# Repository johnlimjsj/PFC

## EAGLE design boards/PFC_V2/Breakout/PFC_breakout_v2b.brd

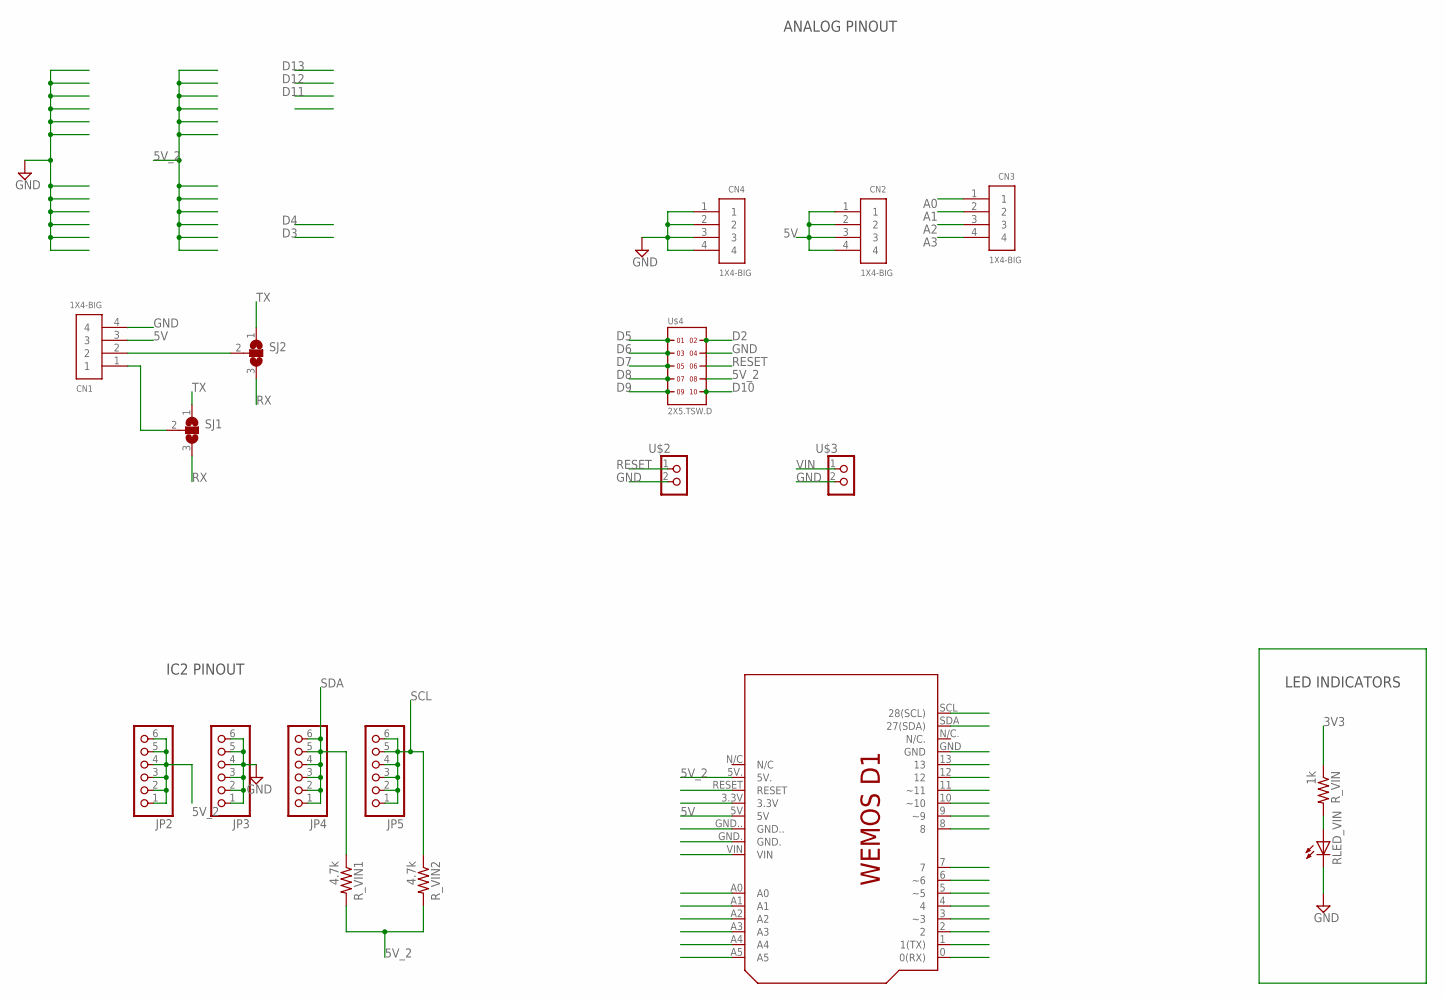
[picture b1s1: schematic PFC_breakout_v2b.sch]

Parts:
CN1, CN2, CN3, CN4: 1X4-BIG; 1X04-BIG
JP2, JP3, JP4, JP5: PINHD-1X6; 1X06
RLED_VIN: LEDCHIP-LED0603; CHIP-LED0603
R_VIN: 1k; R0603
R_VIN1, R_VIN2: 4.7k; R0603
SJ1, SJ2: SJ2W; SJ_2
U$1: WEMOS-D1SHIELD; WEMOS-D1
U$2, U$3: PINHD-2X1; 2X01
U$4: 2X5.TSW.D; TSW-105-XXX-D-XXX

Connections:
3V3: R_VIN.1, U$1.3.3V
5V: CN1.3, CN2.1, CN2.2, CN2.3, CN2.4, U$1.5V
5V_2: JP2.1, JP2.2, JP2.3, JP2.4, JP2.5, JP2.6, R_VIN1.2, R_VIN2.2, U$1.5V., U$4.8
A0: CN3.1, U$1.A0
A1: CN3.2, U$1.A1
A2: CN3.3, U$1.A2
A3: CN3.4, U$1.A3
A4: U$1.A4
A5: U$1.A5
D2: U$1.2, U$4.2
D3: U$1.3 (~3)
D4: U$1.4
D5: U$1.5 (~5), U$4.1
D6: U$1.6 (~6), U$4.3
D7: U$1.7, U$4.5
D8: U$1.8, U$4.7
D9: U$1.9 (~9), U$4.9
D10: U$1.10 (~10), U$4.10
D11: U$1.11 (~11)
D12: U$1.12
D13: U$1.13
GND: CN1.4, CN4.1, CN4.2, CN4.3, CN4.4, JP3.1, JP3.2, JP3.3, JP3.4, JP3.5, JP3.6, RLED_VIN.C, U$1.GND, U$1.GND., U$1.GND.., U$2.2 (3), U$3.2 (3), U$4.4
unnamed: RLED_VIN.A, R_VIN.2
unnamed: CN1.2, SJ2.2
unnamed: CN1.1, SJ1.2
RESET: U$1.RESET, U$2.1, U$4.6
RX: SJ1.3, SJ2.3, U$1.0 (0(RX))
SCL: JP5.1, JP5.2, JP5.3, JP5.4, JP5.5, JP5.6, R_VIN2.1, U$1.SCL (28(SCL))
SDA: JP4.1, JP4.2, JP4.3, JP4.4, JP4.5, JP4.6, R_VIN1.1, U$1.SDA (27(SDA))
TX: SJ1.1, SJ2.1, U$1.1 (1(TX))
VIN: U$1.VIN, U$3.1

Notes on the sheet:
ANALOG PINOUT
IC2 PINOUT
LED INDICATORS

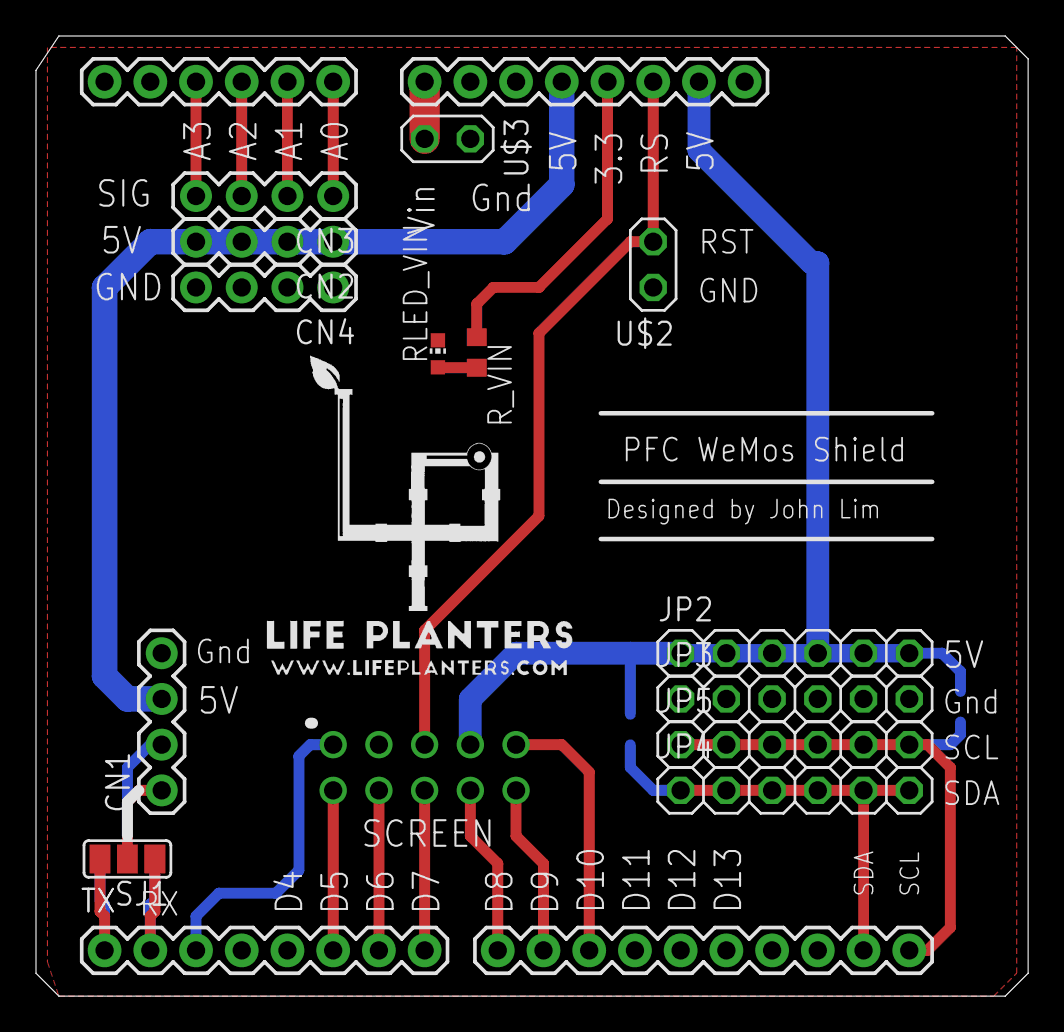
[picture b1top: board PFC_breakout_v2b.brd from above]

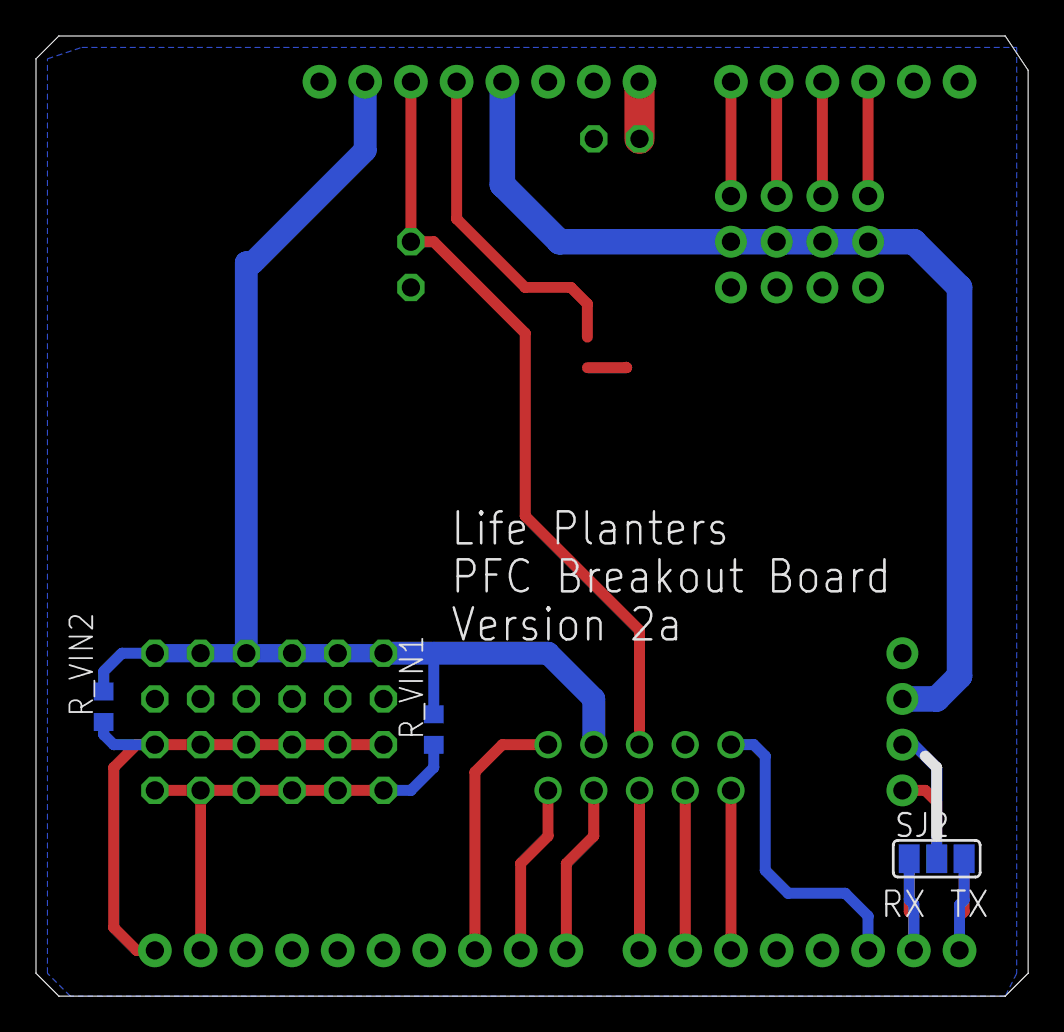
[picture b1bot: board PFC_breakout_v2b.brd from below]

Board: 2 copper layers, 55.1 x 53.3 mm, 18 parts (3 on the bottom side), 24 nets.

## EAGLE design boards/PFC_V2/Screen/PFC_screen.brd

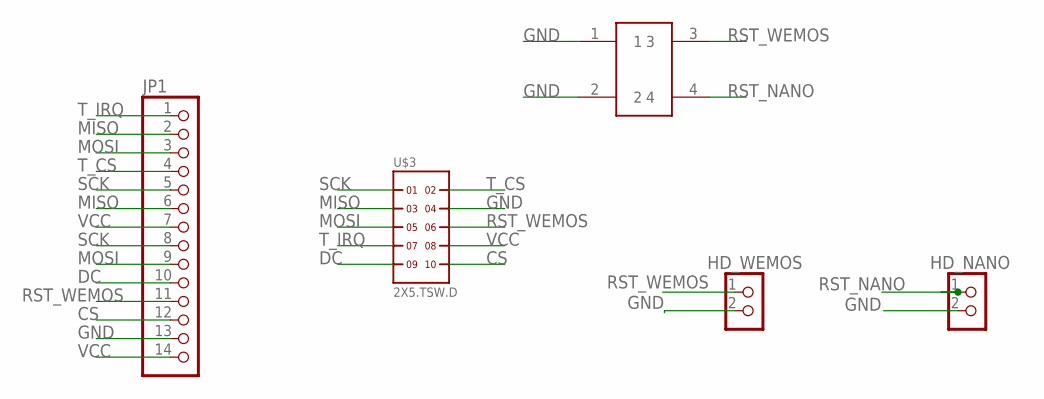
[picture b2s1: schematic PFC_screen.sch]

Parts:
HD_NANO: PINHD-2X1; 2X01
HD_WEMOS: PINHD-2X1; 2X01
JP1: PINHD-1X14-CB; 1X14-CB
U$1: EK1019; EK1019_6X6X5MM
U$3: 2X5.TSW.D; TSW-105-XXX-D-XXX

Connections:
CS: JP1.12, U$3.10
DC: JP1.10, U$3.9
GND: HD_NANO.2 (3), HD_WEMOS.2 (3), JP1.13, U$1.1, U$1.2, U$3.4
MISO: JP1.2, JP1.6, U$3.3
MOSI: JP1.3, JP1.9, U$3.5
RST_NANO: HD_NANO.1, U$1.4
RST_WEMOS: HD_WEMOS.1, JP1.11, U$1.3, U$3.6
SCK: JP1.5, JP1.8, U$3.1
T_CS: JP1.4, U$3.2
T_IRQ: JP1.1, U$3.7
VCC: JP1.7, JP1.14, U$3.8

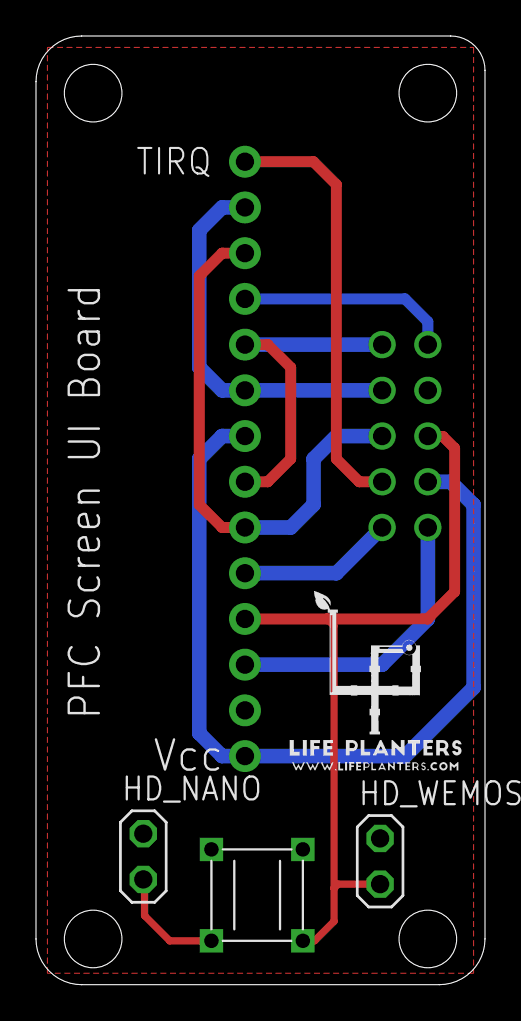
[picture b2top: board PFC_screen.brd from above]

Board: 2 copper layers, 24.9 x 52.7 mm, 5 parts (0 on the bottom side), 11 nets.

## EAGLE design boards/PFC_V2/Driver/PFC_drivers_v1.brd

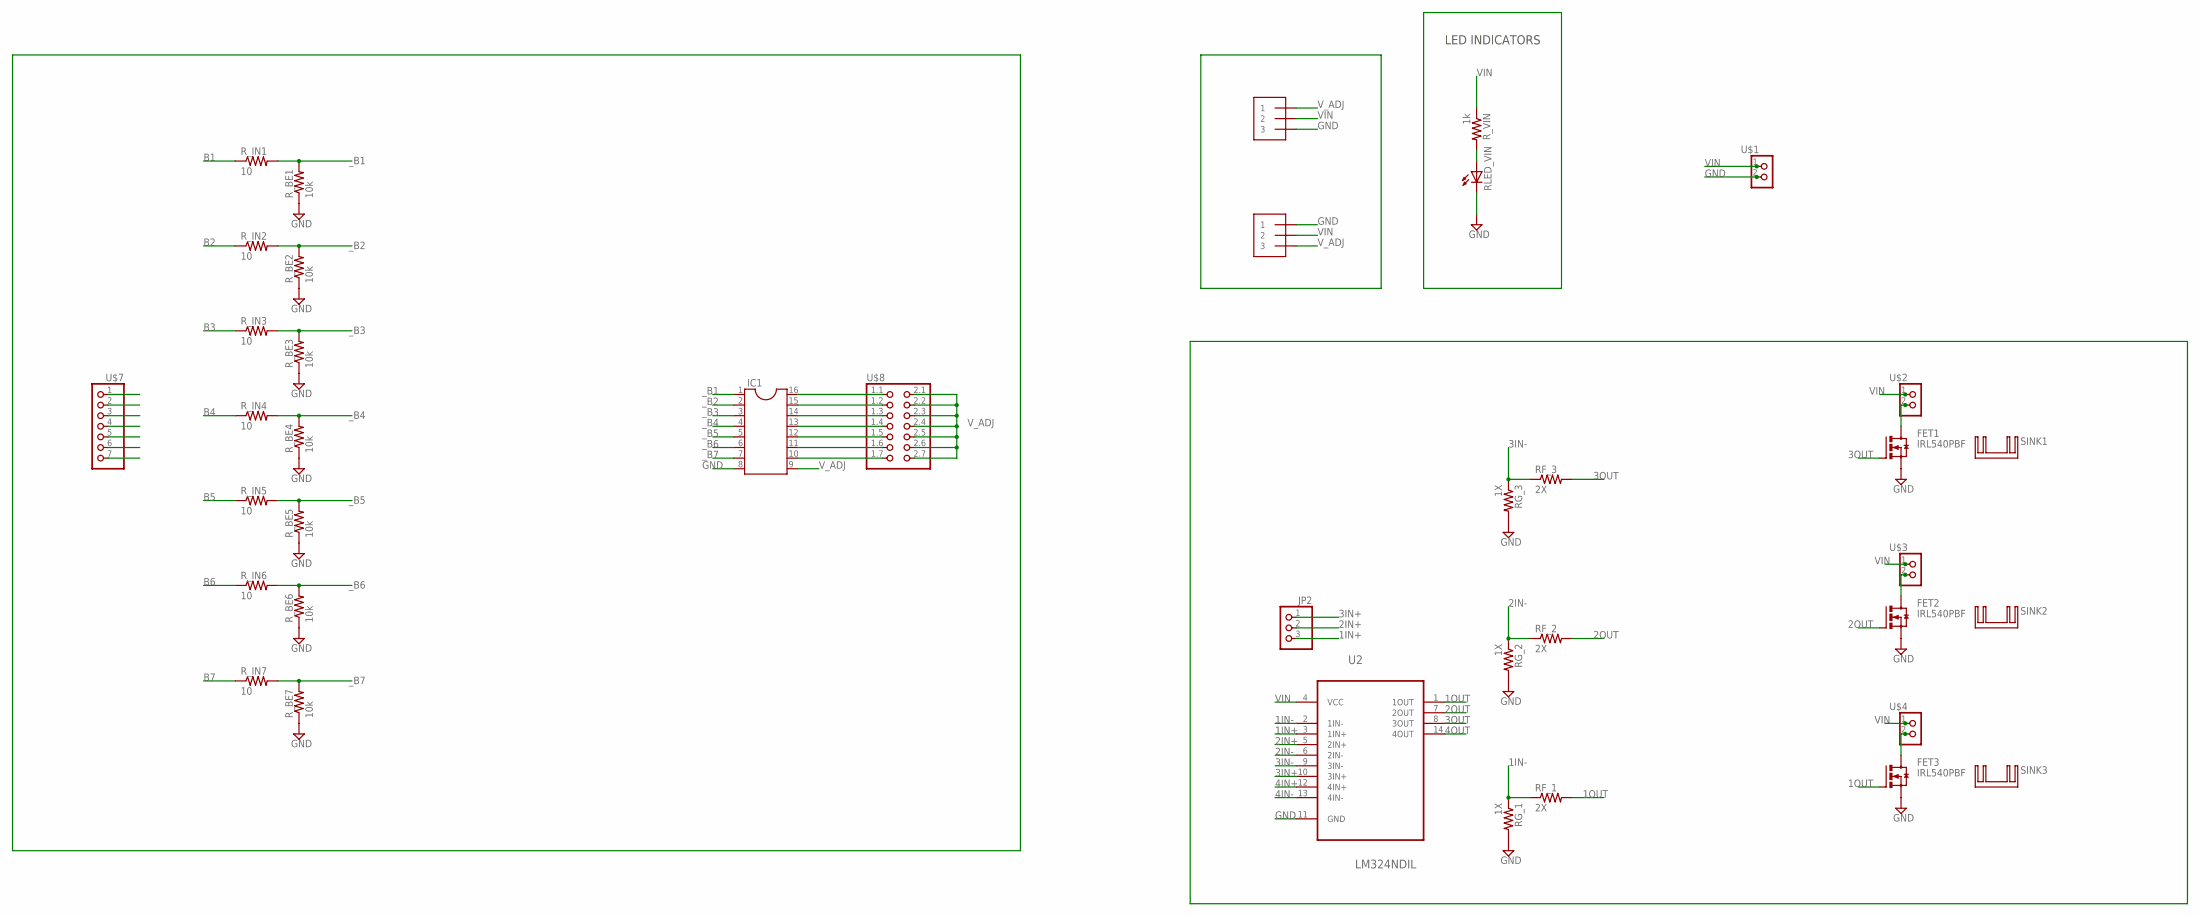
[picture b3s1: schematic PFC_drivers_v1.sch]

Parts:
FET1, FET2, FET3: IRL540PBF; TO220AV
IC1: DIL16S; SOCKET-16
JP2: PINHD-1X3; 1X03
RF_1, RF_2, RF_3: 2X; R0603
RG_1, RG_2, RG_3: 1X; R0603
RLED_VIN: LEDCHIP-LED0603; CHIP-LED0603
R_BE1, R_BE2, R_BE3, R_BE4, R_BE5, R_BE6, R_BE7: 10k; R0603
R_IN1, R_IN2, R_IN3, R_IN4, R_IN5, R_IN6, R_IN7: 10; R0603
R_VIN: 1k; R0603
SINK1, SINK2, SINK3: FW1S
U2: LM324NDIL; DIL14
U$1, U$2, U$3, U$4: PINHD-2X1; 2X01
U$5, U$6: 1X3; 1X3-3.5MM
U$7: PINHD-1X7; 1X07
U$8: PINHD-2X7; 2X07-BIG

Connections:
1IN+: JP2.3, U2.3 (1IN+)
1IN-: RF_1.1, RG_1.1, U2.2 (1IN-)
1OUT: FET3.B (G), RF_1.2, U2.1 (1OUT)
2IN+: JP2.2, U2.5 (2IN+)
2IN-: RF_2.1, RG_2.1, U2.6 (2IN-)
2OUT: FET2.B (G), RF_2.2, U2.7 (2OUT)
3IN+: JP2.1, U2.10 (3IN+)
3IN-: RF_3.1, RG_3.1, U2.9 (3IN-)
3OUT: FET1.B (G), RF_3.2, U2.8 (3OUT)
4IN+: U2.12 (4IN+)
4IN-: U2.13 (4IN-)
4OUT: U2.14 (4OUT)
B1: R_IN1.1, U$7.1
B2: R_IN2.1, U$7.2
B3: R_IN3.1, U$7.3
B4: R_IN4.1, U$7.4
B5: R_IN5.1, U$7.5
B6: R_IN6.1, U$7.6
B7: R_IN7.1, U$7.7
GND: FET1.E (S), FET2.E (S), FET3.E (S), IC1.8, RG_1.2, RG_2.2, RG_3.2, RLED_VIN.C, R_BE1.1, R_BE2.1, R_BE3.1, R_BE4.1, R_BE5.1, R_BE6.1, R_BE7.1, U2.11 (GND), U$1.2 (3), U$5.3, U$6.1
unnamed: RLED_VIN.A, R_VIN.2
unnamed: IC1.10, U$8.1.7
unnamed: IC1.11, U$8.1.6
unnamed: IC1.12, U$8.1.5
unnamed: IC1.13, U$8.1.4
unnamed: IC1.14, U$8.1.3
unnamed: IC1.15, U$8.1.2
unnamed: IC1.16, U$8.1.1
unnamed: FET1.C (D), U$2.2 (3)
unnamed: FET2.C (D), U$3.2 (3)
unnamed: FET3.C (D), U$4.2 (3)
VIN: R_VIN.1, U2.4 (VCC), U$1.1, U$2.1, U$3.1, U$4.1, U$5.2, U$6.2
V_ADJ: IC1.9, U$5.1, U$6.3, U$8.2.1, U$8.2.2, U$8.2.3, U$8.2.4, U$8.2.5, U$8.2.6, U$8.2.7
_B1: IC1.1, R_BE1.2, R_IN1.2
_B2: IC1.2, R_BE2.2, R_IN2.2
_B3: IC1.3, R_BE3.2, R_IN3.2
_B4: IC1.4, R_BE4.2, R_IN4.2
_B5: IC1.5, R_BE5.2, R_IN5.2
_B6: IC1.6, R_BE6.2, R_IN6.2
_B7: IC1.7, R_BE7.2, R_IN7.2

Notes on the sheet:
LED INDICATORS

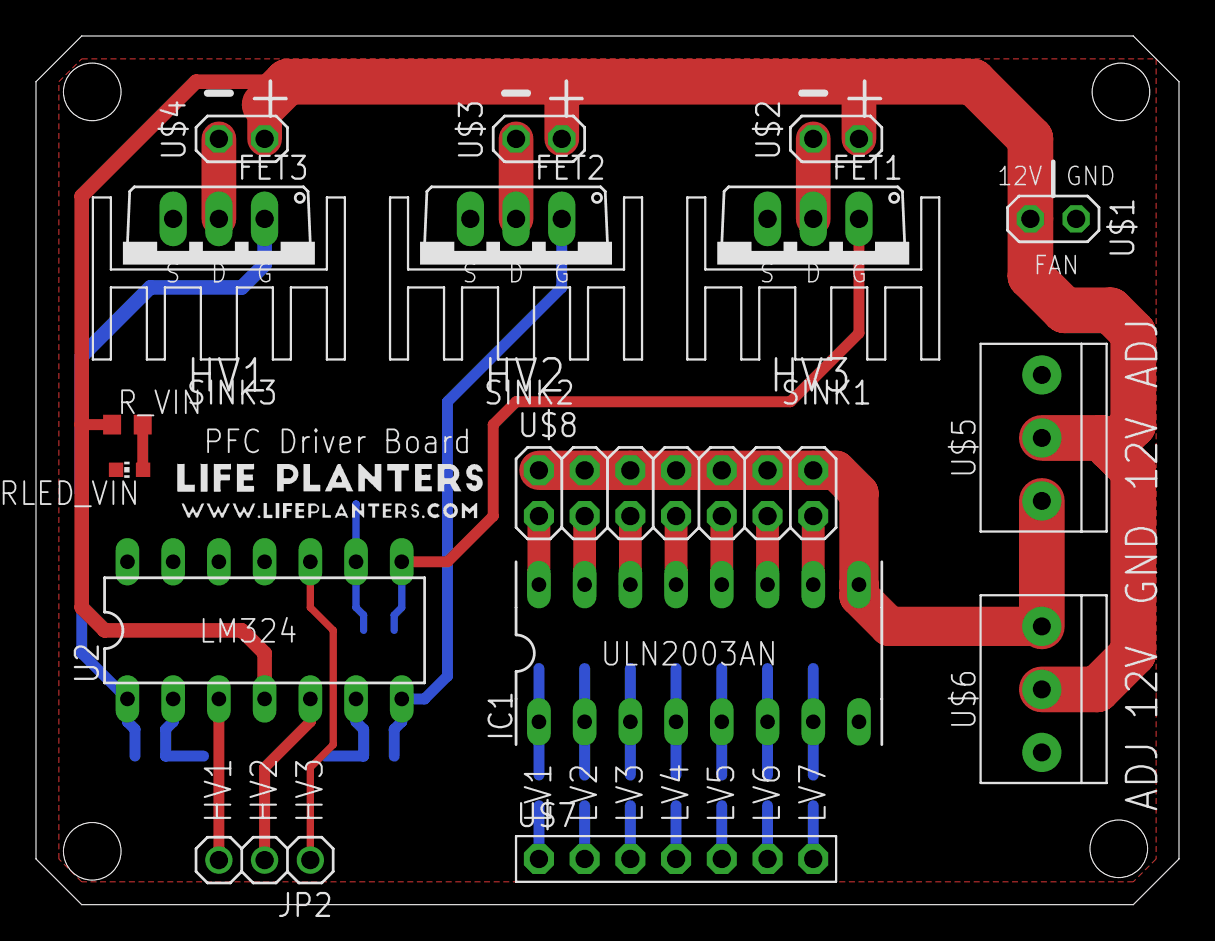
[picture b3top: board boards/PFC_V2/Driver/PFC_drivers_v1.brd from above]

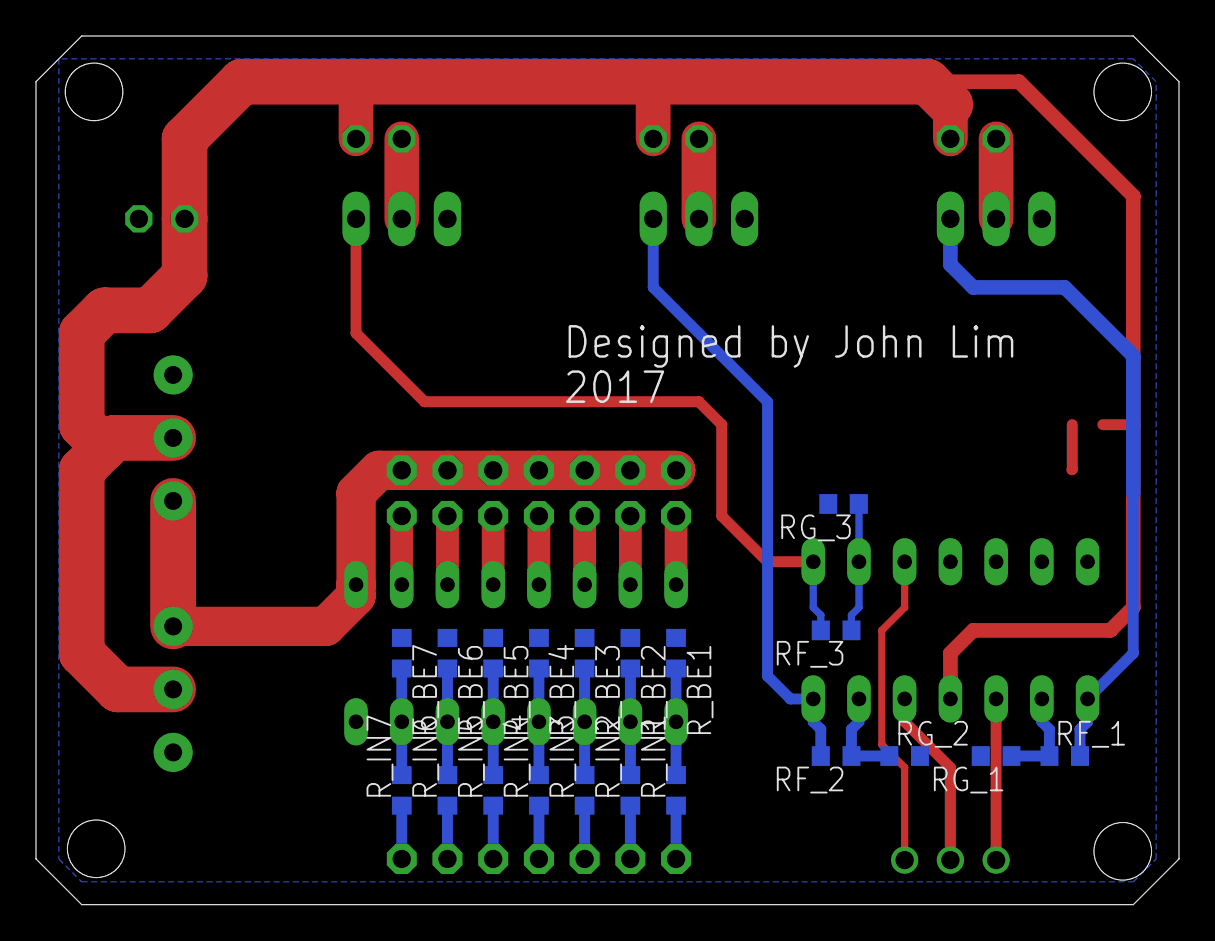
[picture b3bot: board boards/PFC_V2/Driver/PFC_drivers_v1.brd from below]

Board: 2 copper layers, 63.5 x 48.3 mm, 39 parts (20 on the bottom side), 37 nets.

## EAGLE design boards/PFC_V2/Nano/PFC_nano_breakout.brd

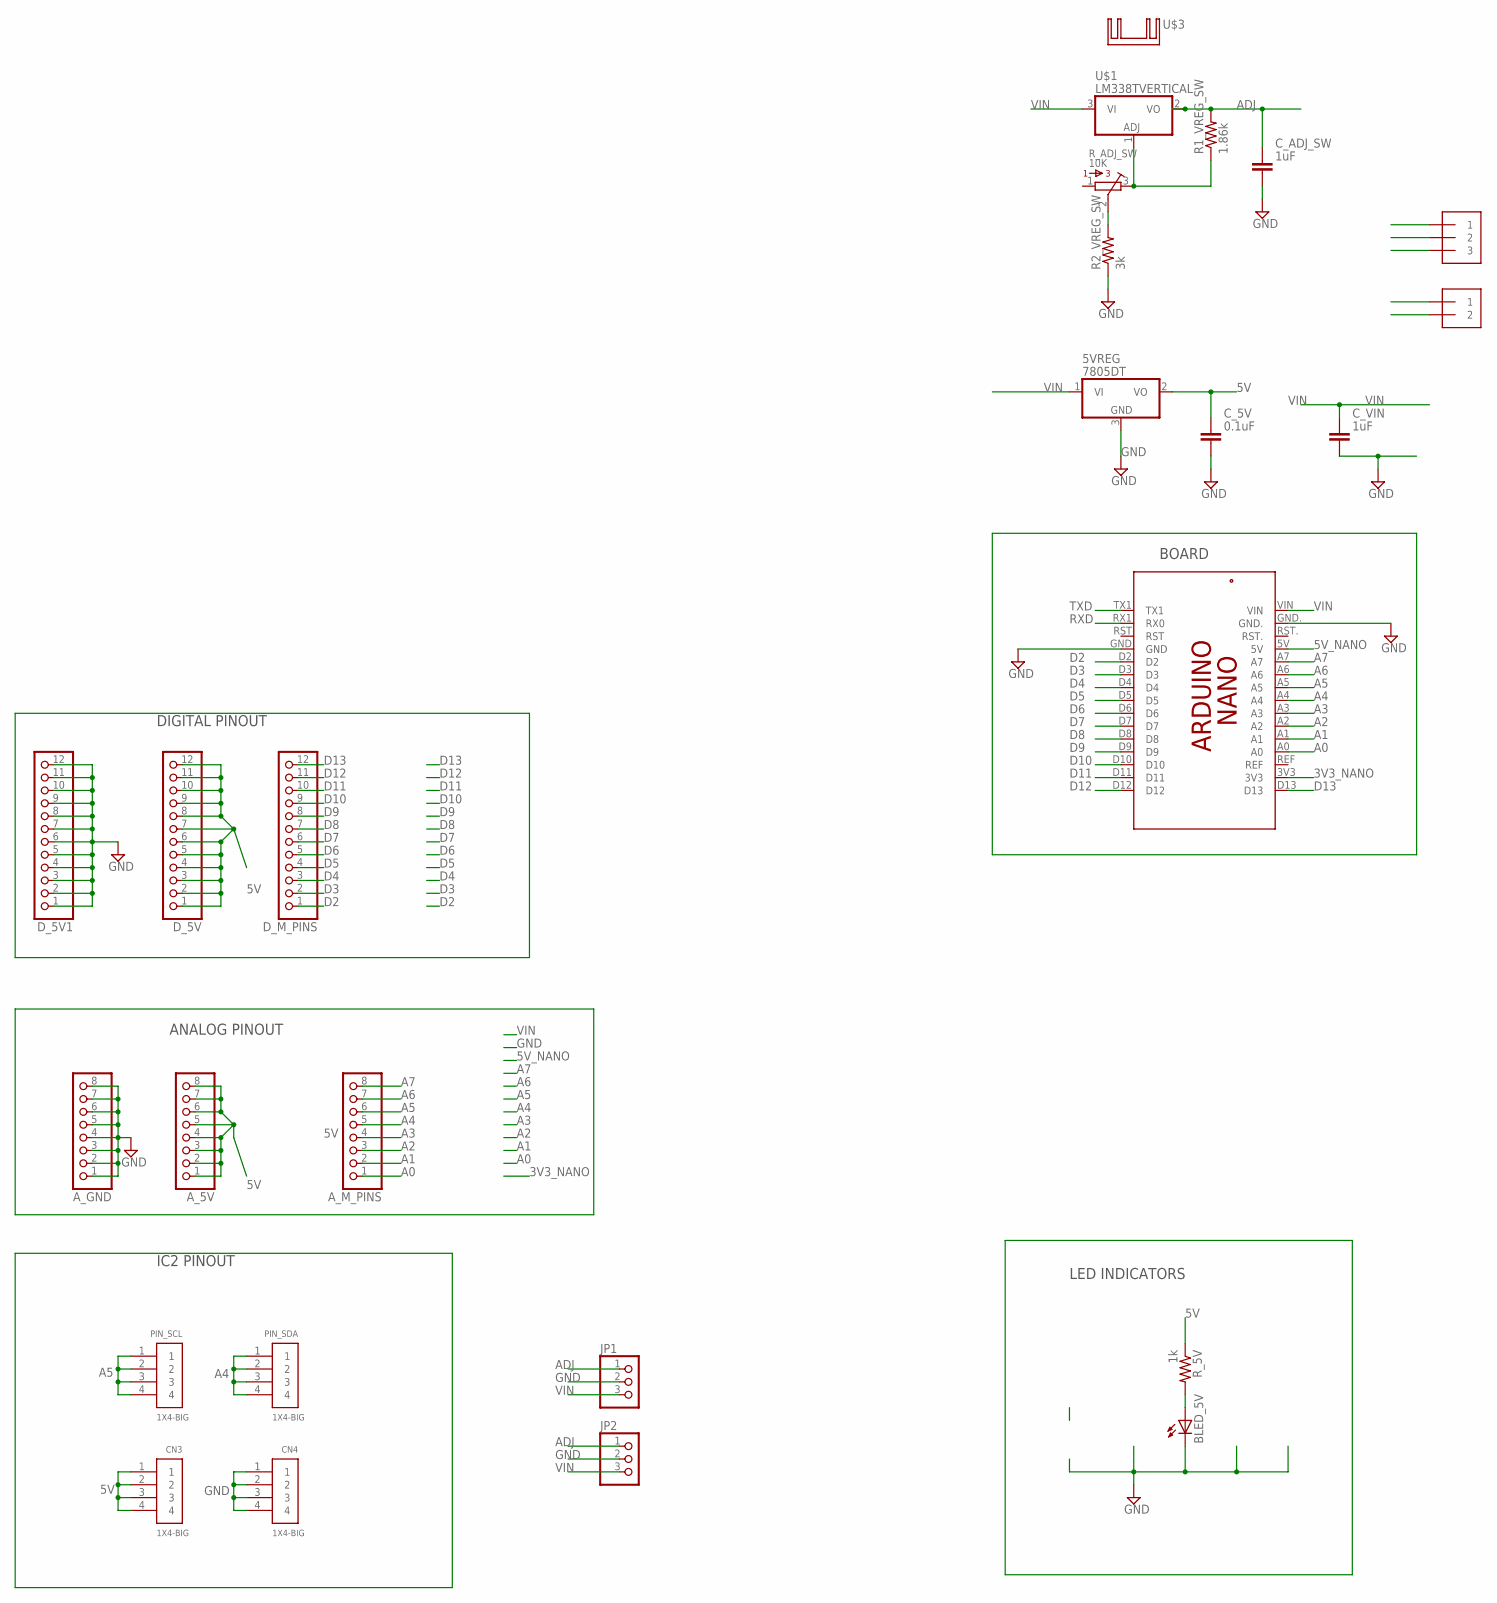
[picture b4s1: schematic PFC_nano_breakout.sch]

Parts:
5VREG: 7805DT; TO252
A_5V: PINHD-1X8CLEANBIG; 1X08-CLEANBIG
A_GND: PINHD-1X8CLEANBIG; 1X08-CLEANBIG
A_M_PINS: PINHD-1X8CLEANBIG; 1X08-CLEANBIG
BLED_5V: LEDCHIP-LED0603; CHIP-LED0603
CN3, CN4: 1X4-BIG; 1X04-BIG
C_5V: 0.1uF; C603
C_ADJ_SW: 1uF; C603
C_VIN: 1uF; C603
D_5V, D_5V1: PINHD-1X12-CB; 1X12-CB
D_M_PINS: PINHD-1X12-CB; 1X12-CB
J2: 1X2-3.5MM
JP1, JP2: PINHD-1X3CB; 1X03-CLEANBIG
PCB1: ARDUINO_NANO_SHIELD
PIN_SCL: 1X4-BIG; 1X04-BIG
PIN_SDA: 1X4-BIG; 1X04-BIG
R1_VREG_SW: 1.86k; R0603
R2_VREG_SW: 3k; R0603
R_5V: 1k; R0603
R_ADJ_SW: 10K; 3386P
U$1: LM338TVERTICAL; TO220V
U$2: 1X3; 1X3-3.5MM
U$3: FW1S; FW1S-DOCU

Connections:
3V3_NANO: PCB1.3V3
5V: 5VREG.2 (VO), A_5V.1, A_5V.2, A_5V.3, A_5V.4, A_5V.5, A_5V.6, A_5V.7, A_5V.8, CN3.1, CN3.2, CN3.3, CN3.4, C_5V.1, D_5V.1, D_5V.2, D_5V.3, D_5V.4, D_5V.5, D_5V.6, D_5V.7, D_5V.8, D_5V.9, D_5V.10, D_5V.11, D_5V.12, R_5V.1
5V_NANO: PCB1.5V
A0: A_M_PINS.1, PCB1.A0
A1: A_M_PINS.2, PCB1.A1
A2: A_M_PINS.3, PCB1.A2
A3: A_M_PINS.4, PCB1.A3
A4: A_M_PINS.5, PCB1.A4, PIN_SDA.1, PIN_SDA.2, PIN_SDA.3, PIN_SDA.4
A5: A_M_PINS.6, PCB1.A5, PIN_SCL.1, PIN_SCL.2, PIN_SCL.3, PIN_SCL.4
A6: A_M_PINS.7, PCB1.A6
A7: A_M_PINS.8, PCB1.A7
ADJ: C_ADJ_SW.1, JP1.1, JP2.1, R1_VREG_SW.2, U$1.2 (VO), U$2.2
D2: D_M_PINS.1, PCB1.D2
D3: D_M_PINS.2, PCB1.D3
D4: D_M_PINS.3, PCB1.D4
D5: D_M_PINS.4, PCB1.D5
D6: D_M_PINS.5, PCB1.D6
D7: D_M_PINS.6, PCB1.D7
D8: D_M_PINS.7, PCB1.D8
D9: D_M_PINS.8, PCB1.D9
D10: D_M_PINS.9, PCB1.D10
D11: D_M_PINS.10, PCB1.D11
D12: D_M_PINS.11, PCB1.D12
D13: D_M_PINS.12, PCB1.D13
GND: 5VREG.3 (GND), A_GND.1, A_GND.2, A_GND.3, A_GND.4, A_GND.5, A_GND.6, A_GND.7, A_GND.8, BLED_5V.C, CN4.1, CN4.2, CN4.3, CN4.4, C_5V.2, C_ADJ_SW.2, C_VIN.2, D_5V1.1, D_5V1.2, D_5V1.3, D_5V1.4, D_5V1.5, D_5V1.6, D_5V1.7, D_5V1.8, D_5V1.9, D_5V1.10, D_5V1.11, D_5V1.12, J2.1, JP1.2, JP2.2, PCB1.GND, PCB1.GND., R2_VREG_SW.1, U$2.1
unnamed: R2_VREG_SW.2, R_ADJ_SW.2
unnamed: BLED_5V.A, R_5V.2
unnamed: R1_VREG_SW.1, R_ADJ_SW.3, U$1.1 (GND)
RXD: PCB1.RX1 (RX0)
TXD: PCB1.TX1
VIN: 5VREG.1 (VI), C_VIN.1, J2.2, JP1.3, JP2.3, PCB1.VIN, U$1.3 (VI), U$2.3

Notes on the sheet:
DIGITAL PINOUT
ANALOG PINOUT
IC2 PINOUT
BOARD
LED INDICATORS

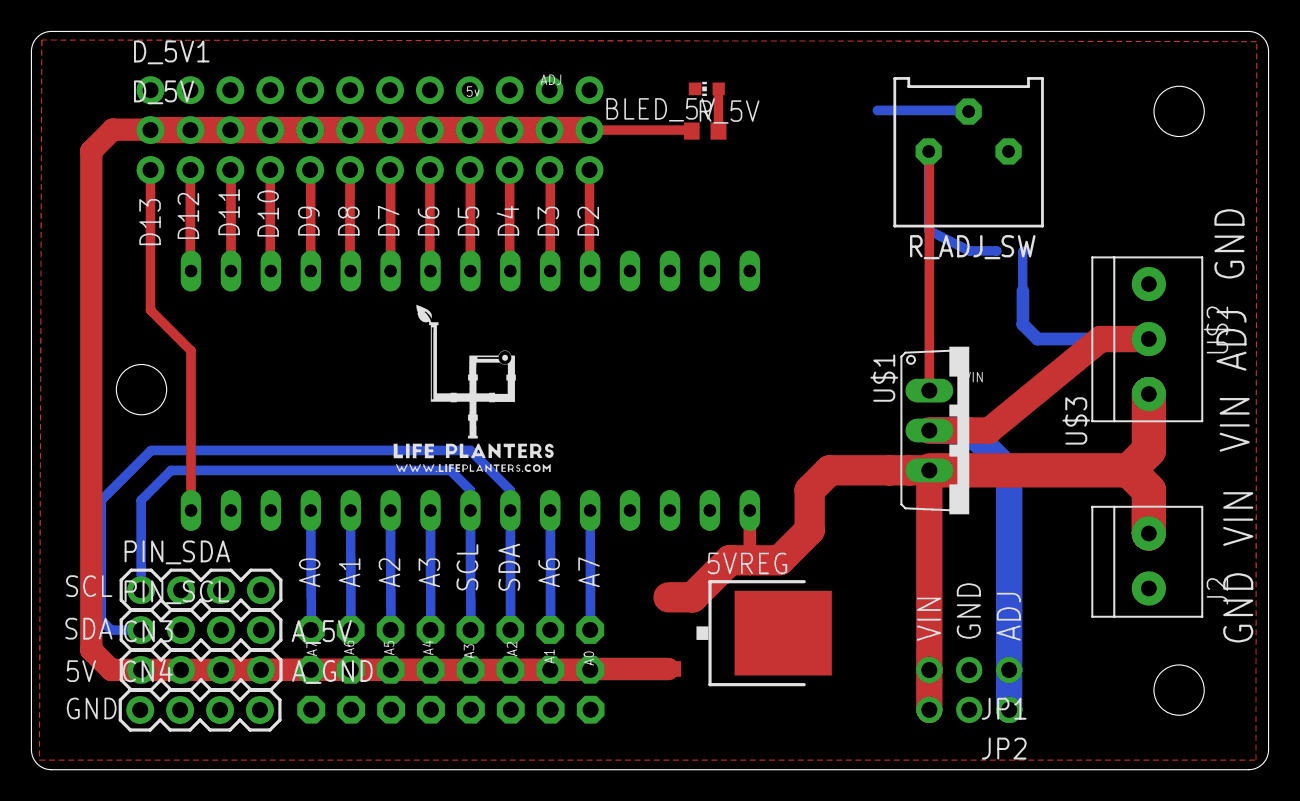
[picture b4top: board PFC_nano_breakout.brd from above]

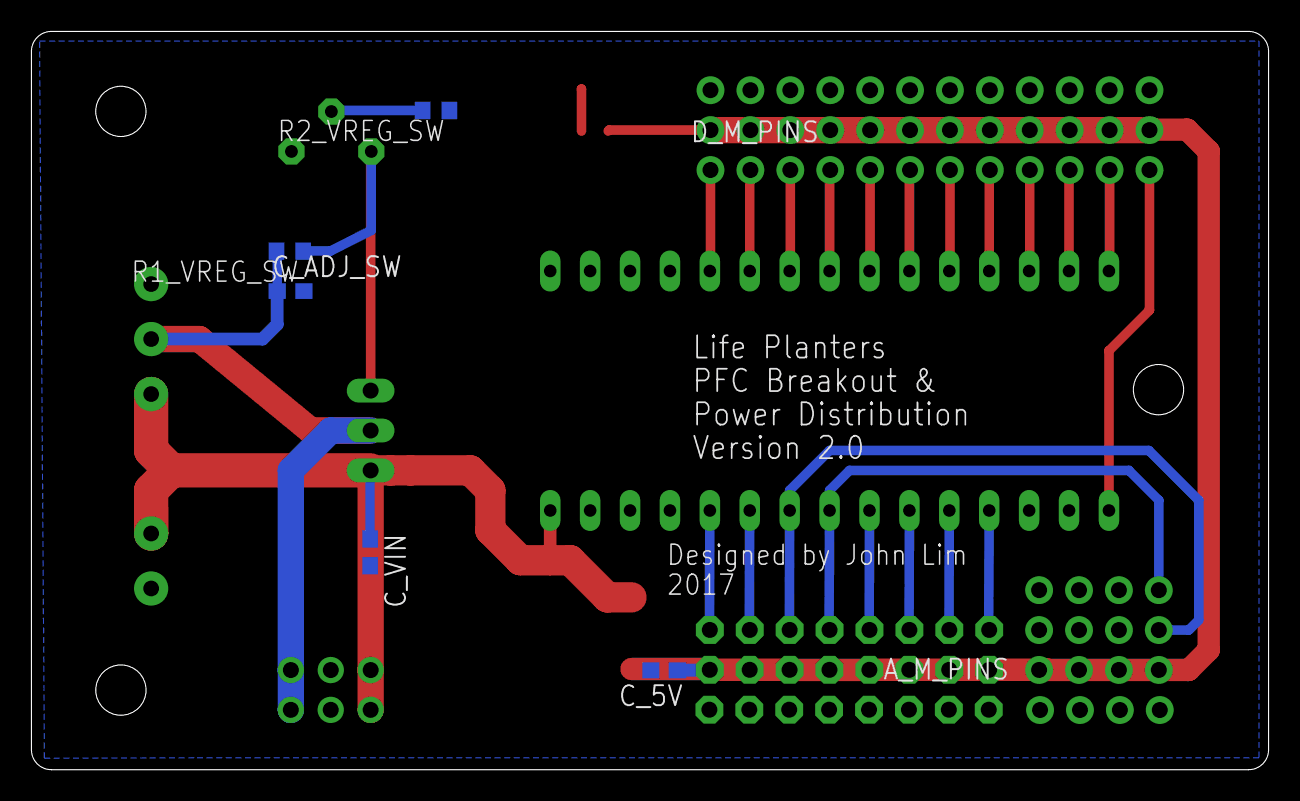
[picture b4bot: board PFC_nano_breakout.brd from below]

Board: 2 copper layers, 78.7 x 47.0 mm, 26 parts (7 on the bottom side), 27 nets.

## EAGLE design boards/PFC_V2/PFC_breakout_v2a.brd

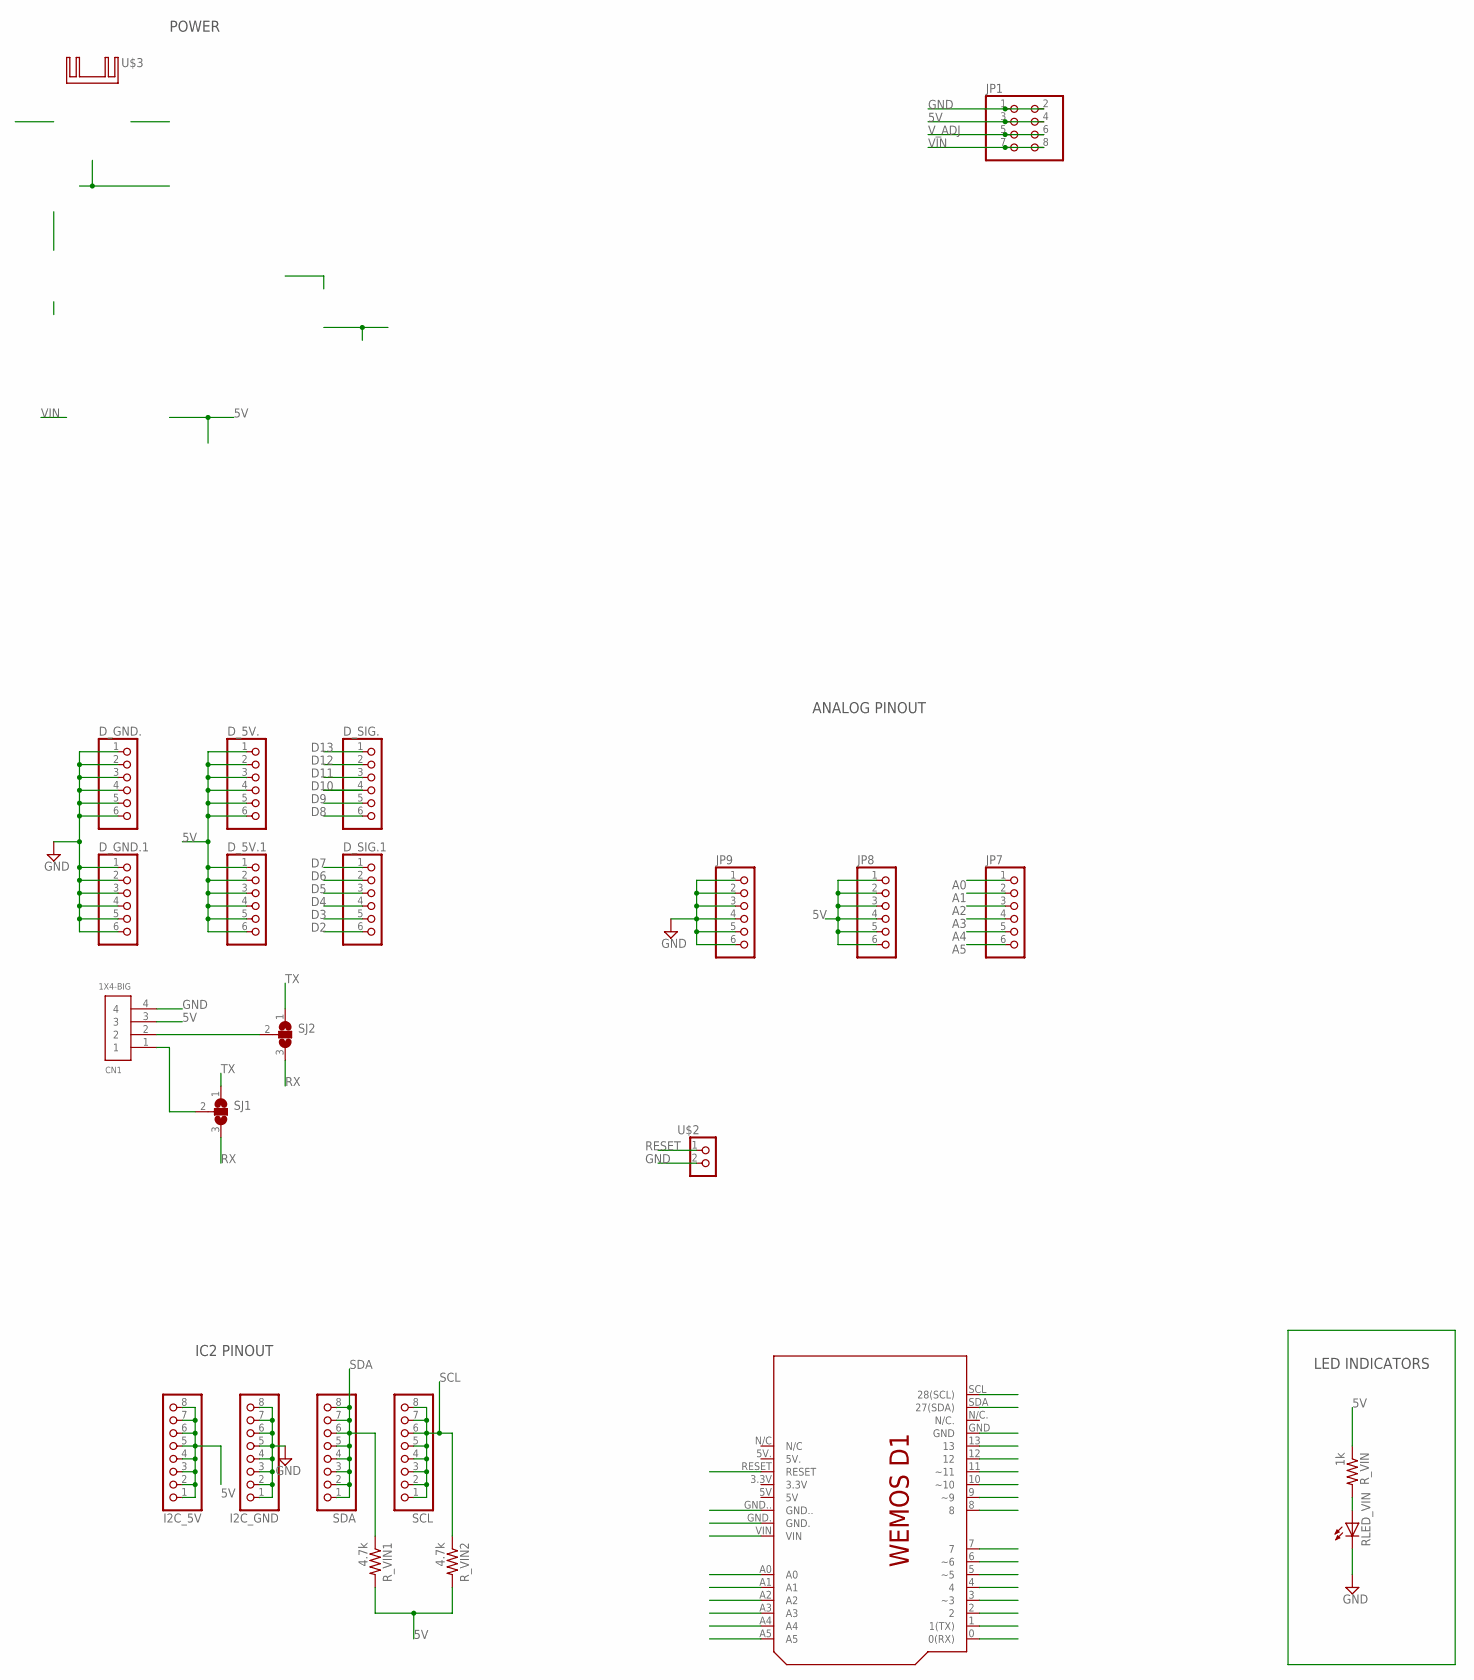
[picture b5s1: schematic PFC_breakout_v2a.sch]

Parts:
CN1: 1X4-BIG; 1X04-BIG
D_5V., D_5V.1: PINHD-1X6; 1X06
D_GND., D_GND.1: PINHD-1X6; 1X06
D_SIG., D_SIG.1: PINHD-1X6; 1X06
I2C_5V, I2C_GND: PINHD-1X8CLEANBIG; 1X08-CLEANBIG
JP1: PINHD-2X4; 2X04
JP7, JP8, JP9: PINHD-1X6; 1X06
RLED_VIN: LEDCHIP-LED0603; CHIP-LED0603
R_VIN: 1k; R0603
R_VIN1, R_VIN2: 4.7k; R0603
SCL: PINHD-1X8CLEANBIG; 1X08-CLEANBIG
SDA: PINHD-1X8CLEANBIG; 1X08-CLEANBIG
SJ1, SJ2: SJ2W; SJ_2
U$1: WEMOS-D1SHIELD; WEMOS-D1
U$2: PINHD-2X1; 2X01
U$3: FW1S; FW1S-DOCU

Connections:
5V: CN1.3, D_5V..1, D_5V..2, D_5V..3, D_5V..4, D_5V..5, D_5V..6, D_5V.1.1, D_5V.1.2, D_5V.1.3, D_5V.1.4, D_5V.1.5, D_5V.1.6, I2C_5V.1, I2C_5V.2, I2C_5V.3, I2C_5V.4, I2C_5V.5, I2C_5V.6, I2C_5V.7, I2C_5V.8, JP1.3, JP1.4, JP8.1, JP8.2, JP8.3, JP8.4, JP8.5, JP8.6, R_VIN.1, R_VIN1.2, R_VIN2.2
A0: JP7.1, U$1.A0
A1: JP7.2, U$1.A1
A2: JP7.3, U$1.A2
A3: JP7.4, U$1.A3
A4: JP7.5, U$1.A4
A5: JP7.6, U$1.A5
D2: D_SIG.1.6, U$1.2
D3: D_SIG.1.5, U$1.3 (~3)
D4: D_SIG.1.4, U$1.4
D5: D_SIG.1.3, U$1.5 (~5)
D6: D_SIG.1.2, U$1.6 (~6)
D7: D_SIG.1.1, U$1.7
D8: D_SIG..6, U$1.8
D9: D_SIG..5, U$1.9 (~9)
D10: D_SIG..4, U$1.10 (~10)
D11: D_SIG..3, U$1.11 (~11)
D12: D_SIG..2, U$1.12
D13: D_SIG..1, U$1.13
GND: CN1.4, D_GND..1, D_GND..2, D_GND..3, D_GND..4, D_GND..5, D_GND..6, D_GND.1.1, D_GND.1.2, D_GND.1.3, D_GND.1.4, D_GND.1.5, D_GND.1.6, I2C_GND.1, I2C_GND.2, I2C_GND.3, I2C_GND.4, I2C_GND.5, I2C_GND.6, I2C_GND.7, I2C_GND.8, JP1.1, JP1.2, JP9.1, JP9.2, JP9.3, JP9.4, JP9.5, JP9.6, RLED_VIN.C, U$1.GND, U$1.GND., U$1.GND.., U$2.2 (3)
unnamed: RLED_VIN.A, R_VIN.2
unnamed: CN1.2, SJ2.2
unnamed: CN1.1, SJ1.2
RESET: U$1.RESET, U$2.1
RX: SJ1.3, SJ2.3, U$1.0 (0(RX))
SCL: R_VIN2.1, SCL.1, SCL.2, SCL.3, SCL.4, SCL.5, SCL.6, SCL.7, SCL.8, U$1.SCL (28(SCL))
SDA: R_VIN1.1, SDA.1, SDA.2, SDA.3, SDA.4, SDA.5, SDA.6, SDA.7, SDA.8, U$1.SDA (27(SDA))
TX: SJ1.1, SJ2.1, U$1.1 (1(TX))
VIN: JP1.7, JP1.8, U$1.VIN
V_ADJ: JP1.5, JP1.6

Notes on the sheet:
ANALOG PINOUT
IC2 PINOUT
POWER
LED INDICATORS

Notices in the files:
parts and their libraries:
SparkFun-Boards: Licensing: Creative Commons ShareAlike 4.0 International - https://creativecommons.org/licenses/by-sa/4.0
microbuilder: This work is placed in the public domain, and may be freely used for commercial and non-commercial work with the following conditions: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
